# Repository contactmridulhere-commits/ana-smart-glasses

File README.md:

# ANA Smart Glasses · V1

**Project Spectra.** AI-native AR glasses, built one version at a time. This repository holds the V1 firmware: an ESP32 heads-up display with vitals sensing that I wore as a daily driver.

**Build video:** [Watch the short](https://www.youtube.com/shorts/zZ5Lkahvl9M)

## What V1 does

- **Heads-up display.** A 128 × 64 SSD1306-class OLED driven over SPI, rendered upside down (`setRotation(2)`) so it reads correctly through the glasses' optic.
- **Heart rate and SpO₂.** A MAX30102 sampled at 400 samples/s. Finger detection, low-pass and high-pass filtering, a differentiator-based beat detector, and SpO₂ from the red/IR ratio through a quadratic calibration curve. Readings are averaged over 5 beats before they are shown.
- **Temperature.** A DHT11 on GPIO 4.
- **Time and date from your phone.** Bluetooth Classic serial (`SerialBT`). Send `T: dd/mm/yyyy hh:mm` once and the glasses keep time from there.

## Hardware

| Part | Role |
|---|---|
| ESP32 devkit | Controller, Bluetooth |
| 128 × 64 OLED (SSD1306 driver, SPI) | Display, seen through the optic |
| MAX30102 | Heart rate and SpO₂ |
| DHT11 | Temperature |

**OLED wiring (SPI):**

| Signal | GPIO |
|---|---|
| MOSI | 23 |
| CLK | 18 |
| DC | 16 |
| CS | 5 |
| RST | 17 |

The MAX30102 uses the default I²C pins (SDA 21, SCL 22). The DHT11 data pin goes to GPIO 4.

## Temple PCBs (V1.1 hardware)

The hand-wired modules are now two custom PCBs shaped like the glasses' temples (straight, then bending down 30° behind the ear). Design files, fabrication outputs and the full write-up are in [`hardware/`](hardware/README.md).

| Board | Temple | What is on it |
|---|---|---|
| `ana-main` | right (display side) | ESP32-U4WDH chip, chip antenna, MAX30102 (faces the skin), SHT40, TTP223 touch, side LED, OLED pads, bring-up pads |
| `ana-power` | left | USB-C on the bottom edge (charging and flashing), CP2102N USB-serial with auto-reset, TP4056 charger, DW01A + FS8205A protection, power path, power and BT-headset switches, side LED, battery pads |

On the temple PCBs the ESP32's in-package flash uses GPIO16/17, and every display and sensor line leaves the chip on the side facing the hinge, so the pins moved. `prototype_toy_.ino` has `#define ANA_TEMPLE_PCB 1` for the PCBs and `0` for the original wiring above.

| Signal | GPIO on the PCB |
|---|---|
| OLED MOSI / CLK / CS | 23 / 4 / 15 |
| OLED DC / RST | 26 / 27 |
| I²C SDA / SCL (MAX30102 + SHT40) | 21 / 22 (unchanged) |
| MAX30102 interrupt | 5 |
| Touch (TTP223 output, also switches the LEDs) | 14 |
| Battery voltage (VSYS / 2; above 4.4 V means USB is plugged in) | 33 |
| Charging (TP4056 status) | 13 |

## Build and flash

1. Install the ESP32 board package in the Arduino IDE.
2. Install the libraries: `Adafruit SSD1306`, `Adafruit GFX`, `MAX3010x` by eepj, and `Adafruit SHT4x` (temple PCBs) or `DHT sensor library` by Adafruit (original wiring).
3. Open `prototype_toy_.ino` with `filters.h` in the same folder, select your ESP32 board and upload. On the temple PCBs, slide the POWER switch on and plug USB-C into the left temple: the CP2102N and auto-reset circuit on the left temple flash the ESP32 over the frame wires, like a devkit.
4. Pair your phone with the Bluetooth device and send the time string once, for example `T: 27/09/2026 18:45`.

## Where it goes next: V2

V2 is in development. It splits the work across two brains: a Raspberry Pi CM5 for vision and on-device AI, and an ESP32-S3 for sensors and power. It swaps the OLED for a reflective-waveguide see-through display. The assistant runs entirely on the frame, with a quantised Phi-3-mini, whisper.cpp speech recognition, Piper TTS and retrieval memory. It also adds continuous two-point ECG through ear-tip electrodes. No cloud anywhere.

More builds: [portfolio](https://portfolio-mridul-six.vercel.app) · [YouTube](https://www.youtube.com/@mridulsharma-martian)

## License

MIT. See [LICENSE](LICENSE).

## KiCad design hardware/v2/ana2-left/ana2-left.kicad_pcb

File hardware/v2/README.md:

# ANA V2 hardware (design stage, not built yet)

V2 moves the glasses from a microcontroller HUD to a wearable Linux computer: binocular waveguide displays, two
cameras, hand-gesture control, on-device speech and small language models, and a full sensor set.
V1.1 (`hardware/ana-main`, `hardware/ana-power`) is untouched; everything for V2 lives in this folder.

**Status:** the three custom boards below are designed, routed and pass the automatic checks. Nothing has been
manufactured or tested. Read "Not verified" before ordering.

## Why a Raspberry Pi and not a Teensy or Portenta

MediaPipe hand tracking, three.js rendering in a browser, speech recognition and language models need a 64-bit
Linux computer with a GPU and gigabytes of RAM. A Teensy 4.1 or Portenta H7 is a microcontroller: about 1 MB of
RAM, no GPU, no browser. The Raspberry Pi Compute Module 5 (4 × Cortex-A76, up to 16 GB RAM, Wi-Fi 5,
Bluetooth 5, 2 camera ports, 2 HDMI outputs) is the strongest module a single builder can buy, solder to nothing
and get software support for. It is 55 × 40 mm, so it cannot go inside a temple: it sits with the battery in a pod
at the back of the head, on a strap between the two ear tips. That also balances the weight of the displays.

## System

```mermaid
flowchart LR
  subgraph FRONT[Front frame]
    WL[Left waveguide + driver]
    WR[Right waveguide + driver]
    CL[Left camera: colour, capture]
    CR[Right camera: NoIR wide, gestures + night vision]
    IR[850 nm IR LEDs + white LEDs]
    NP[Nose-pad electrodes: reference, bias]
  end
  subgraph RT[Right temple: ana2-right]
    IMU[BNO055 9-axis IMU]
    PPG[MAX30102 heart rate + SpO2]
    TMP[TMP117 skin temperature]
    MR[Mic + speaker amp]
    TCH[Touch key]
  end
  subgraph LT[Left temple: ana2-left]
    ML[Mic + speaker amp]
  end
  subgraph POD[Rear pod]
    CM5[Raspberry Pi CM5 on a compact carrier]
    HUB[ana2-pod: ESP32-S3 hub + ADS1299 EEG]
    BAT[Li-ion pack with 5 V output]
  end
  WL & WR -- HDMI --- CM5
  CL & CR -- CSI ribbon --- CM5
  RT -- 16 wires --- HUB
  LT -- 16 wires --- HUB
  HUB -- GPIO: I2C, I2S, UART + USB --- CM5
  NP --- HUB
  BAT --- CM5
  BAT --- HUB
```

| Function | How | Bought or custom |
|---|---|---|
| Compute, Wi-Fi, Bluetooth, storage | Raspberry Pi CM5, 8 GB RAM / 32 GB eMMC, wireless (16 GB / 64 GB for larger models) | bought |
| Carrier for the CM5 | any compact CM5 carrier with 2 CSI camera ports, 2 HDMI (or HDMI + DSI), USB and the 40-pin GPIO signals | bought |
| Displays | 2 waveguide modules with their driver boards, HDMI input | bought (not chosen yet, see below) |
| Cameras | 2 Raspberry Pi-compatible CSI cameras on long ribbons: colour autofocus (capture) and NoIR wide-angle (gestures, night vision) | bought |
| Night vision | 2 × 850 nm IR LEDs per side, PWM-dimmed from the Pi; seen by the NoIR camera, shown in the displays | custom boards + LEDs |
| Head tracking | BNO055, 9-axis with on-chip fusion | `ana2-right` |
| Heart rate, SpO₂, skin temperature | MAX30102, TMP117 (±0.1 °C) | `ana2-right` |
| Voice in / audio out | 2 I²S MEMS microphones (one per side), 2 I²S class-D amplifiers for small speakers by the ears; Bluetooth audio also works | both temple boards |
| Touch | TTP223 key on the right temple | `ana2-right` |
| EEG | ADS1299-4, 4 channels, dry electrodes at both ear tips and both temples, reference and bias on the nose pads | `ana2-pod` |
| Always-on hub | ESP32-S3: power button, battery level, EEG stream over USB, BLE while the Pi is off | `ana2-pod` |
| Power | Li-ion pack with a 5 V / 5 A output and USB-C charging | bought |

## The three custom boards

All are 4-layer, 0.8 mm, parts on one side, JLCPCB-assembled. Every assembled part has an LCSC number that was in
stock on 2026-11-11.

| | `ana2-right` | `ana2-left` | `ana2-pod` |
|---|---|---|---|
| Shape | temple, 104.5 + 39.5 mm, 13.4 → 9.4 mm tall | same outline | 62 × 42 mm, antenna notch |
| Parts | 46 (40 assembled) | 25 (20 assembled) | 74 (63 assembled) |
| Unrouted / unconnected | 0 / 0 | 0 / 0 | 0 / 0 |
| DRC errors | 0 | 0 | 0 |
| DRC warnings | 1 (narrow neck in a ground pour) | 1 (0.3 mm ground stub at the microphone) | 0 |
| ERC | 1 warning (amplifier pad pin type) | 1 warning (same) | 1 warning (pin type on an unused input) |
| Schematic ↔ board | match | match | match |

The V2 temple cover is taller and thicker than V1 (inside 14 / 12 / 10 mm tall, 7 mm thick, in
`config/temple.json`), because the 11.5 mm camera ribbon and the display cable run behind the board.

## Wiring

**Each temple to the pod: two rows of 8 wires, same pad order at both ends** (J1 and J2 on the temple; J1/J2 for
the right and J3/J4 for the left on the pod).

| Pad | 1 | 2 | 3 | 4 | 5 | 6 | 7 | 8 |
|---|---|---|---|---|---|---|---|---|
| Row A | 5V | GND | SDA | SCL | IMU_INT | PPG_INT | TOUCH | IR_PWM |
| Row B | 5V | GND | I2S_BCLK | I2S_LRCLK | MIC_SD | SPK_SD | GND | LED_PWM |

The left temple uses only 5V, GND, IR_PWM and row B.

**Pod to the Raspberry Pi GPIO** (J5, J6):

| Pad | 1 | 2 | 3 | 4 | 5 | 6 | 7 | 8 |
|---|---|---|---|---|---|---|---|---|
| J5 | SDA · GPIO2 | SCL · GPIO3 | IMU_INT · GPIO4 | PPG_INT · GPIO5 | TOUCH · GPIO17 | IR_PWM · GPIO12 | LED_PWM · GPIO13 | GND |
| J6 | BCLK · GPIO18 | LRCLK · GPIO19 | MIC_SD · GPIO20 | SPK_SD · GPIO21 | hub TX → GPIO15 | hub RX ← GPIO14 | PI_SHDN · GPIO6 | GND |

Other pod pads: J7 5 V in from the pack, J8 USB-C (hub to a Pi USB port, or to a PC for flashing), J9 BOOT,
J10 electrodes (1 left ear tip, 2 right ear tip, 3 left temple, 4 right temple, 5 reference, 6 bias, 7 shield),
J11 power button, J12 cell voltage sense and pack enable.

I²C addresses: BNO055 0x28, MAX30102 0x57, TMP117 0x48.

## Software plan

Raspberry Pi OS 64-bit, booting straight into a full-screen Chromium window that runs GestureHolo (MediaPipe
Tasks Vision + three.js) on the gesture camera and spans both displays. Sensors arrive over I²C; audio over I²S
(the `googlevoicehat-soundcard` overlay drives a MAX98357A and an I²S microphone together and is the starting
point). `llama.cpp` with a 1–4 B-parameter quantised model, `whisper.cpp` and Piper run as local services, as in
the V2 notes in the root README. None of this software is written or tested in this repository yet.

Expect, as rough figures to measure rather than promises: hand tracking at 15–30 frames/s, simple three.js scenes
at 30–60 frames/s, a few tokens per second from a 3–4 B model, and not all three at full speed at once.

## Budgets (estimates)

| | Estimate |
|---|---|
| Power | 3 W idle, 6–9 W with camera, tracking and rendering running |
| Run time | about 1.5–2 hours from a 12 Wh (3000 mAh) pack |
| Heat | the CM5 needs a metal heat spreader as the outer face of the pod, away from the head |
| Weight | roughly 180–220 g on the head, about half of it in the rear pod |

## Not verified

- **Displays.** No waveguide module is chosen. The design assumes each comes with a driver board that takes HDMI
  and 5 V. Pick the modules first; they set the frame shape and the front of the temples.
- **Carrier and cables.** The CM5 carrier, camera ribbons (200–300 mm) and HDMI cables are off-the-shelf parts
  that still have to be chosen and fitted. Hinges cannot fold with ribbons through them unless a slack loop is
  designed in.
- **Pin details.** The ADS1299 wiring was checked against its datasheet (bypass values, unused pins, bias
  feedback). The BNO055, MAX98357A, ICS-43434 and TMP117 wiring follows the KiCad library pin maps but was not
  checked against their datasheets here. Check each before ordering.
- **EEG quality.** Dry electrodes on a moving head are noisy. The analog supply is the 5 V rail through an RC
  filter, so EEG is only in specification on battery power (not from USB through the diode). This is not a medical
  device; use it on battery only.
- **IR safety.** 850 nm LEDs are invisible but not harmless. Keep the drive at the designed 80 mA with diffuse
  wide-angle LEDs and do not use lensed high-power emitters.
- **Thermal, RF, audio levels, battery protection.** Not simulated or measured.

## Regenerating

```bash
/usr/bin/python3 hardware/v2/scripts/v2.py
```

`scripts/v2.py` holds the parts, nets and placement of all three boards and uses the V1 generator in
`hardware/scripts` as a library. Outputs: `ana2-*/` (KiCad projects, `drc.json`, `erc.json`), `fab/` (Gerbers,
BOM, pick-and-place), `docs/` (schematic PDFs, renders).

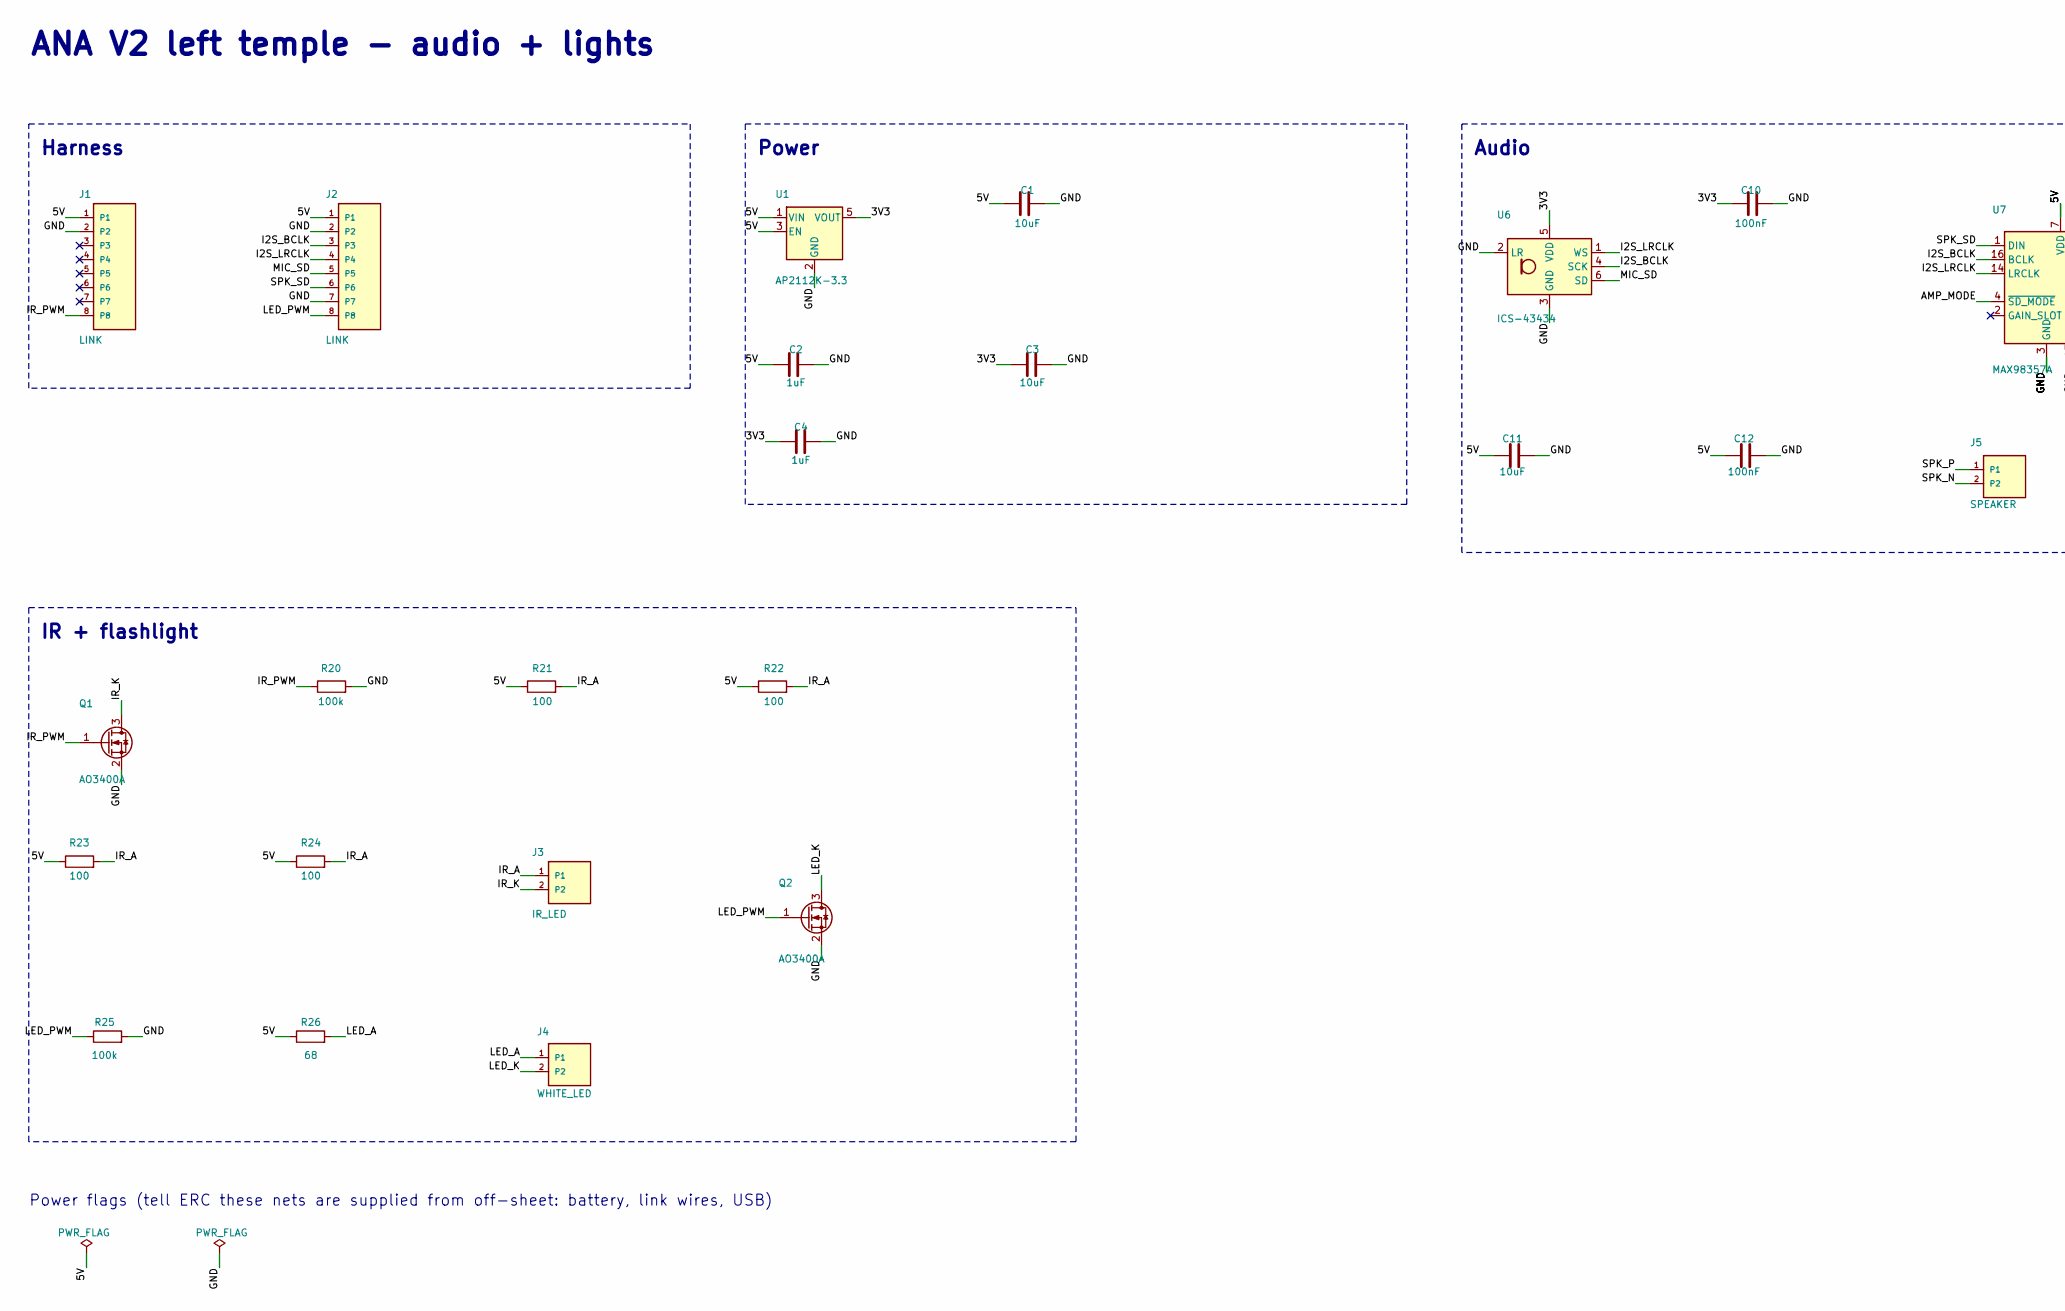
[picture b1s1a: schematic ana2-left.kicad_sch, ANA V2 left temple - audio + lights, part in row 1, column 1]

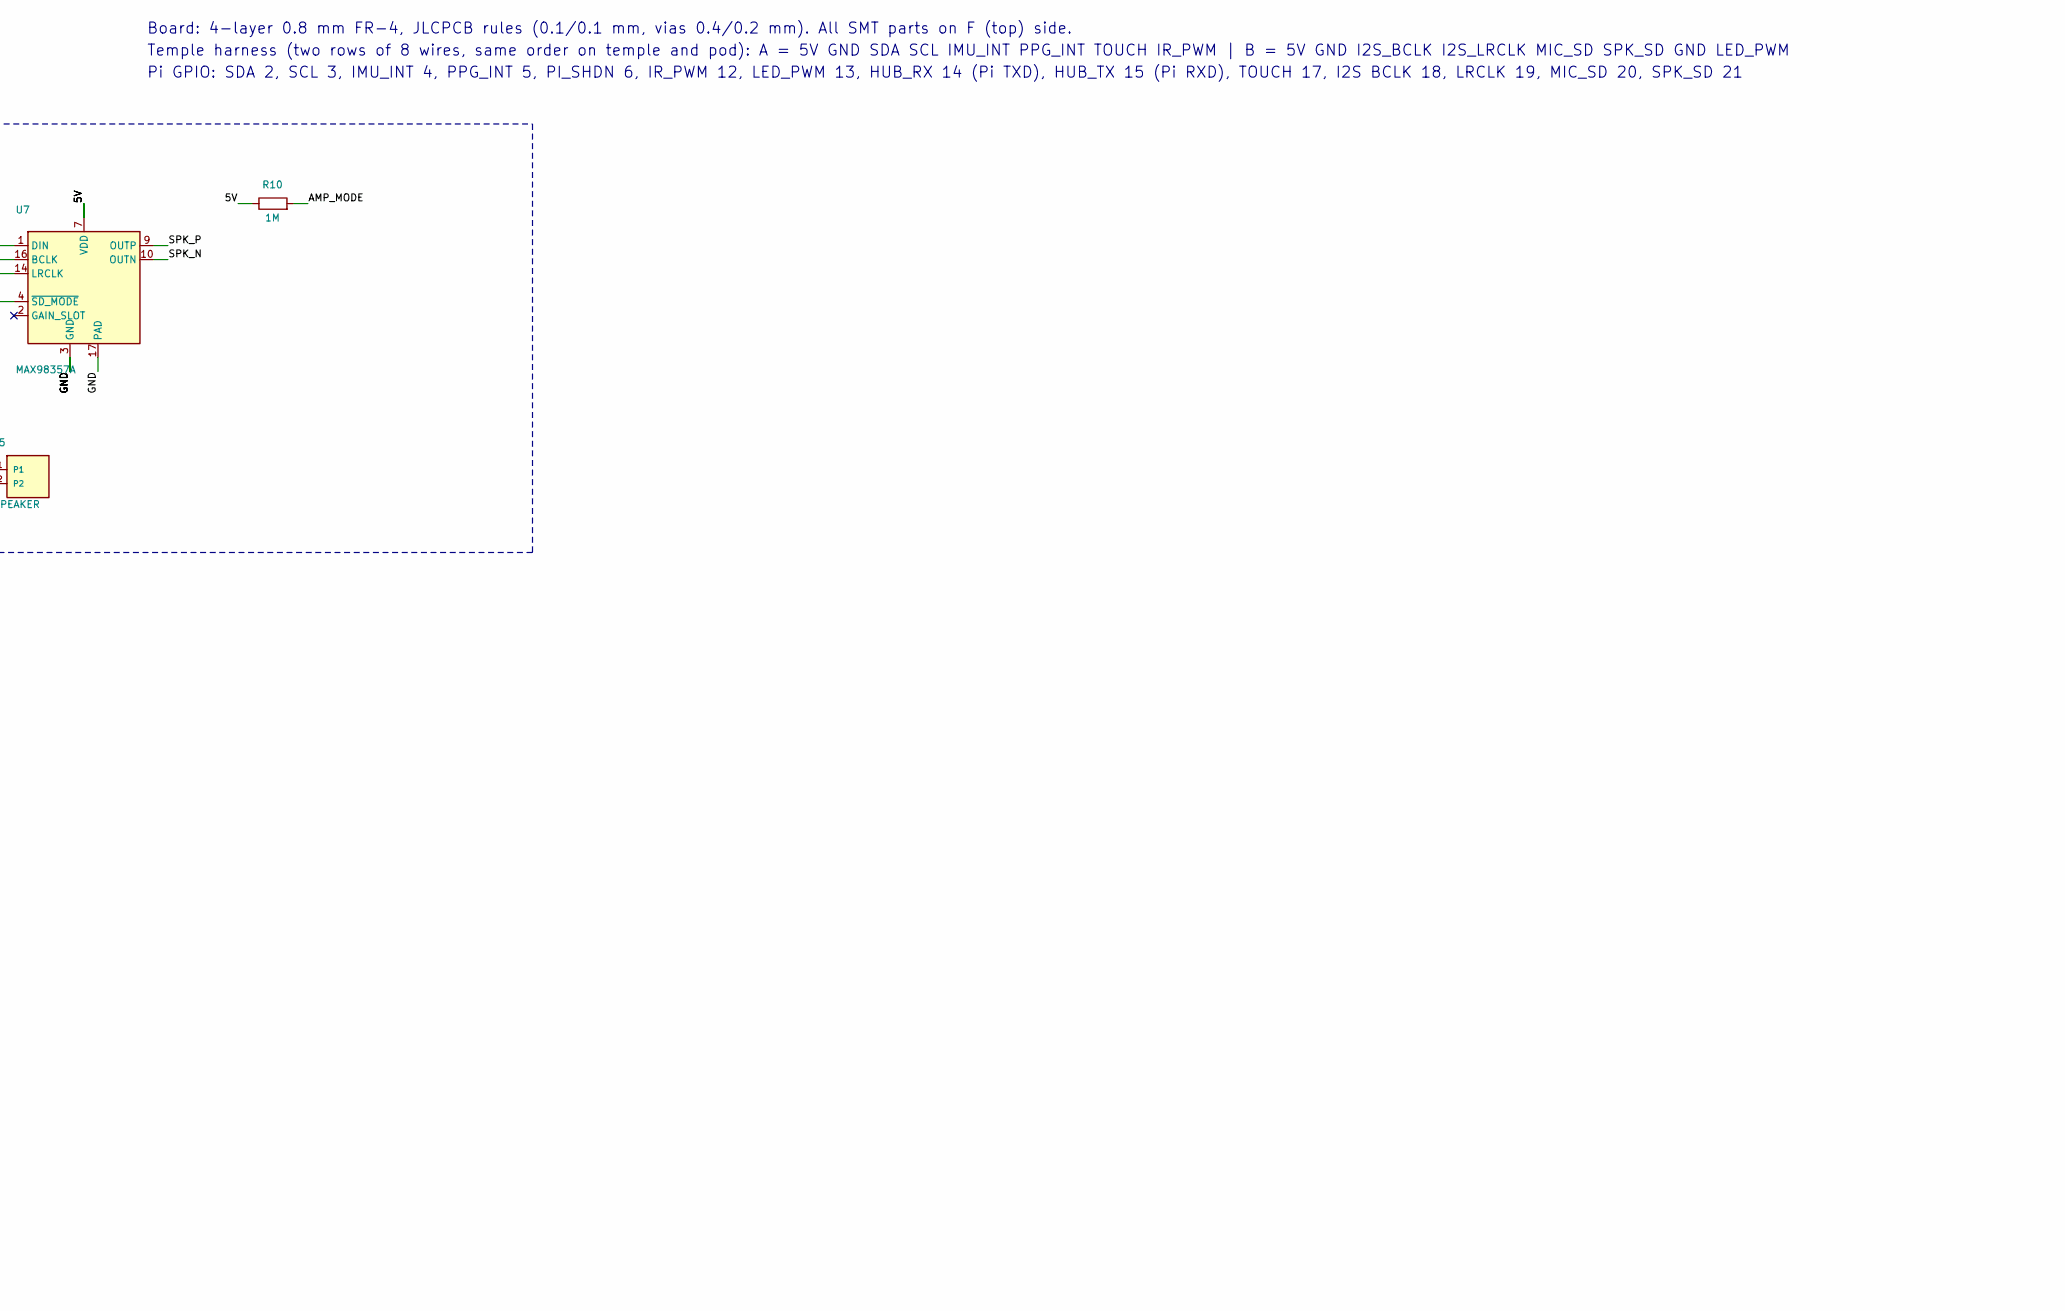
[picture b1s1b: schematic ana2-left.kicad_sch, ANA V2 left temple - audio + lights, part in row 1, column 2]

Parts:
C1, C11: 10uF; C_0603_1608Metric; LCSC C380317
C2, C4: 1uF; C_0402_1005Metric; LCSC C52923
C3: 10uF; C_0402_1005Metric; LCSC C15525
C10, C12: 100nF; C_0402_1005Metric; LCSC C1525
J1, J2: LINK; WirePads_1x08_P1.50mm
J3: IR_LED; WirePads_1x02_P1.50mm
J4: WHITE_LED; WirePads_1x02_P1.50mm
J5: SPEAKER; WirePads_1x02_P1.50mm
Q1, Q2: AO3400A; SOT-23; MPN AO3400A; LCSC C20917
R10: 1M; R_0402_1005Metric; LCSC C26083
R20, R25: 100k; R_0402_1005Metric; LCSC C25741
R21, R22, R23, R24: 100; R_0402_1005Metric; LCSC C25076
R26: 68; R_0402_1005Metric; LCSC C25131
U1: AP2112K-3.3; SOT-23-5; MPN AP2112K-3.3TRG1; LCSC C51118
U6: ICS-43434; InvenSense_ICS-43434-6_3.5x2.65mm; MPN ICS-43434; LCSC C5656610
U7: MAX98357A; TQFN-16-1EP_3x3mm_P0.5mm_EP1.23x1.23mm; MPN MAX98357AETE+T; LCSC C910544

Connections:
/3V3: C3.1, C4.1, C10.1, U1.5 (VOUT), U6.5 (VDD)
/5V: C1.1, C2.1, C11.1, C12.1, J1.1, J2.1, R10.1, R21.1, R22.1, R23.1, R24.1, R26.1, U1.1 (VIN), U1.3 (EN), U7.7 (VDD), U7.8 (VDD)
/AMP_MODE: R10.2, U7.4 (~SD_MODE)
/GND: C1.2, C2.2, C3.2, C4.2, C10.2, C11.2, C12.2, J1.2, J2.2, J2.7, Q1.2 (S), Q2.2 (S), R20.2, R25.2, U1.2 (GND), U6.2 (LR), U6.3 (GND), U7.3 (GND), U7.11 (GND), U7.15 (GND), U7.17 (PAD)
/I2S_BCLK: J2.3, U6.4 (SCK), U7.16 (BCLK)
/I2S_LRCLK: J2.4, U6.1 (WS), U7.14 (LRCLK)
/IR_A: J3.1, R21.2, R22.2, R23.2, R24.2
/IR_K: J3.2, Q1.3 (D)
/IR_PWM: J1.8, Q1.1 (G), R20.1
/LED_A: J4.1, R26.2
/LED_K: J4.2, Q2.3 (D)
/LED_PWM: J2.8, Q2.1 (G), R25.1
/MIC_SD: J2.5, U6.6 (SD)
/SPK_N: J5.2, U7.10 (OUTN)
/SPK_P: J5.1, U7.9 (OUTP)
/SPK_SD: J2.6, U7.1 (DIN)

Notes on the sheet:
ANA V2 left temple - audio + lights
Board: 4-layer 0.8 mm FR-4, JLCPCB rules (0.1/0.1 mm, vias 0.4/0.2 mm). All SMT parts on F (top) side.
Temple harness (two rows of 8 wires, same order on temple and pod): A = 5V GND SDA SCL IMU_INT PPG_INT TOUCH IR_PWM | B = 5V GND I2S_BCLK I2S_LRCLK MIC_SD SPK_SD GND LED_PWM
Pi GPIO: SDA 2, SCL 3, IMU_INT 4, PPG_INT 5, PI_SHDN 6, IR_PWM 12, LED_PWM 13, HUB_RX 14 (Pi TXD), HUB_TX 15 (Pi RXD), TOUCH 17, I2S BCLK 18, LRCLK 19, MIC_SD 20, SPK_SD 21
Harness
Power
Audio
IR + flashlight
Power flags (tell ERC these nets are supplied from off-sheet: battery, link wires, USB)

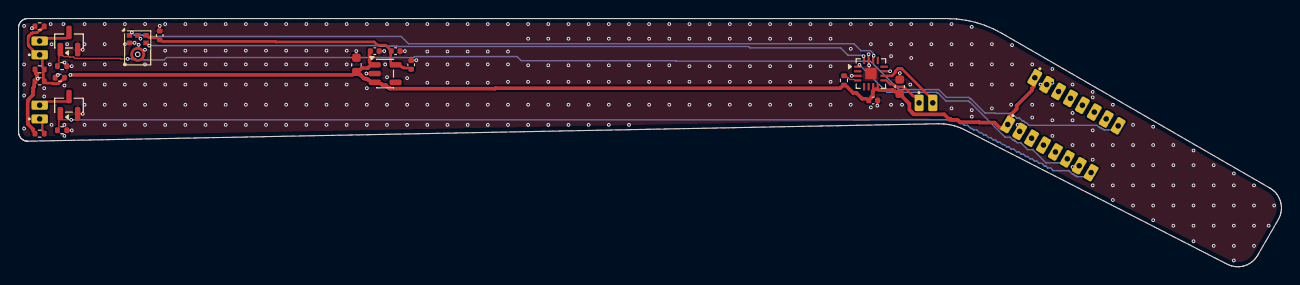
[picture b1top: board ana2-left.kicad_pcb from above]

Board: 4 copper layers, 137.8 x 27.1 mm, 25 parts (0 on the bottom side), 16 nets.

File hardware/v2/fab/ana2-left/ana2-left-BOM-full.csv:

Ref,Value,Footprint,LCSC,MPN,Fitted by,Note
J1,LINK,ana:WirePads_1x08_P1.50mm,,,you (wire/pad),"to the pod, row A (same order as the right temple; only 5V GND IR_PWM used)"
J2,LINK,ana:WirePads_1x08_P1.50mm,,,you (wire/pad),"to the pod, row B: 5V GND BCLK LRCLK MIC_SD SPK_SD GND LED_PWM"
U1,AP2112K-3.3,Package_TO_SOT_SMD:SOT-23-5,C51118,AP2112K-3.3TRG1,JLCPCB,3.3 V for the sensors and microphone
C1,10uF,Capacitor_SMD:C_0603_1608Metric,C380317,,JLCPCB,5 V entry bulk
C2,1uF,Capacitor_SMD:C_0402_1005Metric,C52923,,JLCPCB,
C3,10uF,Capacitor_SMD:C_0402_1005Metric,C15525,,JLCPCB,
C4,1uF,Capacitor_SMD:C_0402_1005Metric,C52923,,JLCPCB,
U6,ICS-43434,Sensor_Audio:InvenSense_ICS-43434-6_3.5x2.65mm,C5656610,ICS-43434,JLCPCB,"I2S MEMS microphone, sound port through the board; this one is the left channel"
C10,100nF,Capacitor_SMD:C_0402_1005Metric,C1525,,JLCPCB,
U7,MAX98357A,Package_DFN_QFN:TQFN-16-1EP_3x3mm_P0.5mm_EP1.23x1.23mm,C910544,MAX98357AETE+T,JLCPCB,"I2S class-D speaker amplifier, 9 dB gain (GAIN pin open)"
R10,1M,Resistor_SMD:R_0402_1005Metric,C26083,,JLCPCB,SD_MODE = 0.45 V: plays (left + right) / 2
C11,10uF,Capacitor_SMD:C_0603_1608Metric,C380317,,JLCPCB,
C12,100nF,Capacitor_SMD:C_0402_1005Metric,C1525,,JLCPCB,
J5,SPEAKER,ana:WirePads_1x02_P1.50mm,,,you (wire/pad),8 ohm micro speaker next to the ear (+ / -)
Q1,AO3400A,Package_TO_SOT_SMD:SOT-23,C20917,AO3400A,JLCPCB,IR illuminator switch (PWM)
R20,100k,Resistor_SMD:R_0402_1005Metric,C25741,,JLCPCB,off while the Pi boots
R21,100,Resistor_SMD:R_0402_1005Metric,C25076,,JLCPCB,4 x 100R = 25R: about 80 mA through two 850 nm LEDs in series
R22,100,Resistor_SMD:R_0402_1005Metric,C25076,,JLCPCB,
R23,100,Resistor_SMD:R_0402_1005Metric,C25076,,JLCPCB,
R24,100,Resistor_SMD:R_0402_1005Metric,C25076,,JLCPCB,
J3,IR_LED,ana:WirePads_1x02_P1.50mm,,,you (wire/pad),two 850 nm IR LEDs in series beside the camera (+ / -)
Q2,AO3400A,Package_TO_SOT_SMD:SOT-23,C20917,AO3400A,JLCPCB,flashlight switch (PWM)
R25,100k,Resistor_SMD:R_0402_1005Metric,C25741,,JLCPCB,
R26,68,Resistor_SMD:R_0402_1005Metric,C25131,,JLCPCB,"white LED, about 28 mA"
J4,WHITE_LED,ana:WirePads_1x02_P1.50mm,,,you (wire/pad),white flashlight LED at the frame corner (+ / -)
